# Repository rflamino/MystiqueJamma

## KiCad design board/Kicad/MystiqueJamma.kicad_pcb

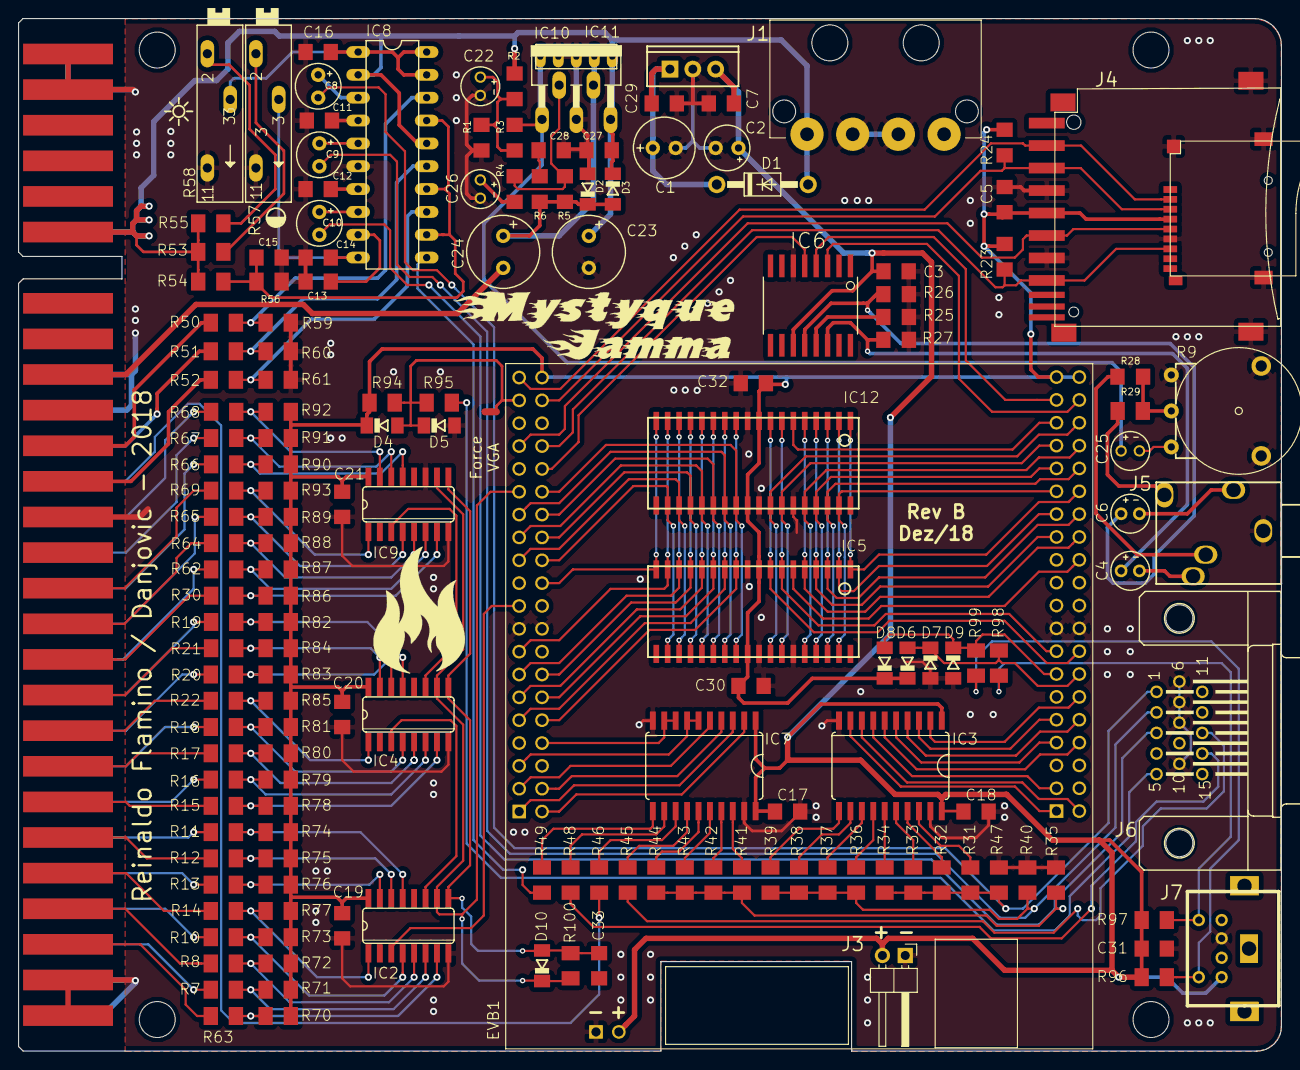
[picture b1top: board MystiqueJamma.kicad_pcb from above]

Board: 2 copper layers, 140.4 x 114.8 mm, 164 parts (0 on the bottom side), 171 nets.

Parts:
C1: 100uF; E2,5-7
C2, C8, C9, C10: 10uF; E2,5-5
C3, C5, C7, C11, C12, C13, C14, C15, C16, C17, C18, C19, C20, C21, C27, C29, C30, C31, C32: 100nF; C1206
C4, C6: 4.7uF; E2-4
C22: 22u; E2-4
C23: 100u/25V; E3,5-8
C24: 1000u/25V; E3,5-8
C25: 10uF; E2-4
C26: 2u2; E2-4
C28: 220nF; C1206
C33: 10n; C1206
D1: 1N4004; DO41-10
D2, D3: 1N4004; SOD80C
D4, D5, D6, D7, D8, D9, D10: 4148; SOD80C
EVB1: C4E6-K; E6V33_BELOW
IC1: 7805; TO220-IGO
IC2, IC4, IC9: 74HC4021D; SO16
IC3, IC7: 74LS245DW; SO20W
IC5, IC12: CY7C1049CV33; SOJV36-400
IC6: TDA1543T; SOIC-16NW
IC8: TLS1233; DIL20
IC10: TDA2030V; CB360
IC11: LA4425V; LA4425
J1: Conn_01x04; Molex_Mega-Fit_76829-0004_2x02_P5.70mm_Vertical
J2: Micro_SD_Card; 9P-SMD-W_-RING
J3: FPGA PWR; PinHeader_1x02_P2.54mm_Horizontal
J4: SDMMC06132; 06132
J5: 1503_09
J6: HF15H; HDF15H
J7: Mini-DIN-6; Mini_din6
K1: JAMMA-EDGE-MYSTIQUE; JAMMA-FULL
R1, R2, R3: 100k; R1206
R4, R28: 4k7; R1206
R5: 150k; R1206
R6: 1R; R1206
R7, R8, R10, R11, R12, R13, R14, R15, R16, R17, R18, R19, R20, R21, R22, R30, R35, R45, R46, R48, R49, R50, R51, R52, R62, R63, R64, R65, R66, R67, R68, R69, R95: 330; M1206
R9: 50k; M1001
R23, R24: 10k; R1206
R25: 1k; R1206
R26, R27: 2k; R1206
R29, R100: 4k7; M1206
R31, R36, R41: 420; M1206
R32, R37, R42: 785; M1206
R33, R38, R43: 1380; M1206
R34, R39, R44: 2230; M1206
R40, R47: 125; M1206
R53, R54, R55, R70, R71, R72, R73, R74, R75, R76, R77, R78, R79, R80, R81, R82, R83, R84, R85, R86, R87, R88, R89, R90, R91, R92, R93, R94: 10k; M1206
R56: 5k; M1206
R57, R58: 5k; SP19L
R59, R60, R61: 430; M1206
R96, R97: 2K2; M1206
R98, R99: 120; M1206

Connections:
+3V3: C5.1, C19.1, C20.1, C21.1, C30.1, C32.1, D4.C, D6.C, D8.C, EVB1.VCC1, EVB1.VCC2, EVB1.VCC3, IC2.16, IC4.16, IC5.9, IC5.27, IC9.16, IC12.9, IC12.27, J2.4, J4.4, R23.2, R24.2, R70.2, R71.2, R72.2, R73.2, R74.2, R75.2, R76.2, R77.2, R78.2, R79.2, R80.2, R81.2, R82.2, R83.2, R84.2, R85.2, R86.2, R87.2, R88.2, R89.2, R90.2, R91.2, R92.2, R93.2, R94.2
+5V: C2.+, C3.1, C7.1, C17.1, C18.1, C31.1, EVB1.5VCC, IC1.OUT, IC3.1, IC3.20, IC6.11, IC7.1, IC7.20, J3.2, J7.5, R96.2, R97.2
+12V: C23.+, C27.1, D1.A, D3.C, IC8.2, IC8.16, IC10.5, IC11.5, J1.1, K1.6, K1.F, R2.1, R53.2, R54.2, R55.2
/AUD-IN: C25.+, IC10.1, IC11.1, R3.2
/B0: EVB1.I0_30, IC7.2
/B1: EVB1.I0_28, IC7.3
/B2: EVB1.I0_32, IC7.4
/B3: EVB1.I0_31, IC7.5
/BURST_GATE: IC8.11, R49.2
/CNTR_CK_LAT: D10.C, EVB1.I0_68, IC2.10, IC4.10, IC9.10, R100.1
/CNTR_DAT: EVB1.I0_53, IC2.3
/COINSW1: K1.16, R69.2
/COINSW2: K1.T, R66.2
/DAC_VREF: IC6.13, R25.2
/G0: EVB1.I0_143, IC3.6
/G1: EVB1.I0_7, IC3.7
/G2: EVB1.I0_10, IC3.8
/G3: EVB1.I0_11, IC3.9
/HSY: EVB1.I0_33, IC7.6, IC7.7
/I2S_BCK: EVB1.I0_103, IC6.3
/I2S_DATA: EVB1.I0_71, IC6.5
/I2S_WS: EVB1.I0_101, IC6.4
/JAMMA-BLUE: K1.13, R52.2
/JAMMA-CSYNC: K1.P, R46.2
/JAMMA-GREEN: K1.N, R51.2
/JAMMA-RED: K1.12, R50.2
/JAMMA_AUDIO: R9.2, R28.2, R29.2
/JAMMA_SPK+: C24.-, K1.10
/LATCH: C33.1, D10.A, IC2.9, IC4.9, IC9.9, R100.2
/L_A: C6.+, IC6.12, R26.2
/L_AUDIO: C6.-, J5.2
/P1B1: K1.22, R15.2
/P1B2: K1.23, R12.2
/P1B3: K1.24, R14.2
/P1B4: K1.25, R8.2
/P1B5: K1.26, R63.2
/P1DW: K1.19, R21.2
/P1LH: K1.20, R22.2
/P1RH: K1.21, R17.2
/P1START: K1.17, R64.2
/P1UP: K1.18, R30.2
/P2B1: K1.Z, R16.2
/P2B2: K1.#A, R11.2
/P2B3: K1.#B, R13.2
/P2B4: K1.#C, R10.2
/P2B5: K1.#D, R7.2
/P2DW: K1.W, R19.2
/P2LH: K1.X, R20.2
/P2RH: K1.Y, R18.2
/P2START: K1.U, R65.2
/P2UP: K1.V, R62.2
/R0: EVB1.I0_137, IC3.2
/R1: EVB1.I0_142, IC3.3
/R2: EVB1.I0_141, IC3.4
/R3: EVB1.I0_144, IC3.5
/R_A: C4.+, IC6.14, R27.2
/R_AUDIO: C4.-, J5.3
/SD_CNT_SCLK: EVB1.I0_72, J2.5, J4.5
/SD_CS: EVB1.I0_100, J2.2, J4.1
/SD_DATAIN: EVB1.I0_99, J2.3, J4.2, R24.1
/SD_DATAOUT: EVB1.I0_88, J2.7, J4.7, R23.1
/SERVICE_SW: K1.R, R68.2
/SRAM_A0: EVB1.I0_114, IC5.1, IC12.1
/SRAM_A1: EVB1.I0_115, IC5.2, IC12.2
/SRAM_A2: EVB1.I0_119, IC5.3, IC12.3
/SRAM_A3: EVB1.I0_120, IC5.4, IC12.4
/SRAM_A4: EVB1.I0_121, IC5.5, IC12.5
/SRAM_A5: EVB1.I0_44, IC5.14, IC12.14
/SRAM_A6: EVB1.I0_50, IC5.15, IC12.15
/SRAM_A7: EVB1.I0_49, IC5.16, IC12.16
/SRAM_A8: EVB1.I0_51, IC5.17, IC12.17
/SRAM_A9: EVB1.I0_58, IC5.18, IC12.18
/SRAM_A10: EVB1.I0_60, IC5.20, IC12.20
/SRAM_A11: EVB1.I0_59, IC5.21, IC12.21
/SRAM_A12: EVB1.I0_65, IC5.22, IC12.22
/SRAM_A13: EVB1.I0_64, IC5.23, IC12.23
/SRAM_A14: EVB1.I0_67, IC5.24, IC12.24
/SRAM_A15: EVB1.I0_110, IC5.32, IC12.32
/SRAM_A16: EVB1.I0_111, IC5.33, IC12.33
/SRAM_A17: EVB1.I0_112, IC5.34, IC12.34
/SRAM_A18: EVB1.I0_113, IC5.35, IC12.35
/SRAM_CE1: EVB1.I0_125, IC5.6
/SRAM_CE2: EVB1.I0_104, IC12.6
/SRAM_IO0: EVB1.I0_133, IC5.7, IC12.7
/SRAM_IO1: EVB1.I0_132, IC5.8, IC12.8
/SRAM_IO2: EVB1.I0_43, IC5.11, IC12.11
/SRAM_IO3: EVB1.I0_42, IC5.12, IC12.12
/SRAM_IO4: EVB1.I0_66, IC5.25, IC12.25
/SRAM_IO5: EVB1.I0_69, IC5.26, IC12.26
/SRAM_IO6: EVB1.I0_105, IC5.29, IC12.29
/SRAM_IO7: EVB1.I0_106, IC5.30, IC12.30
/SRAM_WE: EVB1.I0_46, IC5.13, IC12.13
/TILT: K1.S, R67.2
/VGA-BLUE: C10.-, J6.3, R35.2, R41.2, R42.2, R43.2, R44.2
/VGA-GREEN: C9.-, J6.2, R36.2, R37.2, R38.2, R39.2, R40.2
/VGA-HSYNC: J6.13, R45.2
/VGA-RED: C8.-, J6.1, R31.2, R32.2, R33.2, R34.2, R47.2
/VGA-VSYNC: J6.14, R48.2
/VGA_DETECT: J6.5, R95.2
/VGA_DET_IN: D4.A, D5.C, EVB1.I0_91, R94.1, R95.1
/VSY: EVB1.I0_39, IC7.8, IC7.9
GND: C1.-, C2.-, C3.2, C5.2, C7.2, C11.2, C12.2, C13.2, C14.2, C15.2, C16.2, C17.2, C18.2, C19.2, C20.2, C21.2, C22.-, C23.-, C26.-, C27.2, C28.2, C29.2, C30.2, C31.2, C32.2, D2.A, D5.A, D7.A, D9.A, EVB1.GND1, EVB1.GND2, EVB1.GND3, EVB1.GND4, EVB1.GND5, IC1.GND, IC2.8, IC3.10, IC3.19, IC4.8, IC5.10, IC5.28, IC5.31, IC6.6, IC7.10, IC7.19, IC8.6, IC9.8, IC9.11, IC10.3, IC11.2, IC11.3, IC12.10, IC12.28, IC12.31, J1.2, J1.3, J2.6, J2.SHL@1, J2.SHL@2, J2.SHL@3, J3.1, J4.3, J4.6, J4.GP, J4.GP2, J5.1, J6.6, J6.7, J6.8, J6.10, J7.3, K1.1, K1.2, K1.14, K1.27, K1.28, K1.#E, K1.#F, K1.A, K1.B, K1.L, K1.M, R1.2, R9.1, R9.G1, R9.G2, R25.1, R26.1, R27.1, R35.1, R40.1, R47.1, R56.1, R57.A, R58.A, R59.1, R60.1, R61.1
unnamed: C1.+, C29.1, D1.C, IC1.IN
unnamed: C8.+, IC8.3
unnamed: C9.+, IC8.5
unnamed: C10.+, IC8.8
unnamed: C11.1, IC8.4
unnamed: C12.1, IC8.7
unnamed: C13.1, IC8.9
unnamed: C14.1, IC8.10, R57.S
unnamed: C15.1, IC8.12, IC8.14, IC8.17, R54.1, R56.2
unnamed: C16.1, IC8.1, IC8.19, IC8.20, R58.S
unnamed: C22.+, R1.1, R2.2, R3.1
unnamed: C24.+, D2.C, D3.A, IC10.4, IC11.4, R5.1, R6.1
unnamed: C25.-, R9.3
unnamed: C26.+, R4.2
unnamed: C28.1, R6.2
unnamed: IC2.1, R14.1, R77.1
unnamed: IC2.4, R10.1, R73.1
unnamed: IC2.5, R8.1, R72.1
unnamed: IC2.6, R7.1, R71.1
unnamed: IC2.7, R63.1, R70.1
unnamed: IC2.11, IC4.3
unnamed: IC2.13, R11.1, R74.1
unnamed: IC2.14, R12.1, R75.1
unnamed: IC2.15, R13.1, R76.1
unnamed: IC3.11, R39.1
unnamed: IC3.12, R38.1
unnamed: IC3.13, R37.1
unnamed: IC3.14, R36.1
unnamed: IC3.15, R34.1
unnamed: IC3.16, R33.1
unnamed: IC3.17, R32.1
unnamed: IC3.18, R31.1
unnamed: IC4.1, R22.1, R85.1
unnamed: IC4.4, R18.1, R81.1
unnamed: IC4.5, R17.1, R80.1
unnamed: IC4.6, R16.1, R79.1
unnamed: IC4.7, R15.1, R78.1
unnamed: IC4.11, IC9.3
unnamed: IC4.13, R19.1, R82.1
unnamed: IC4.14, R20.1, R83.1
unnamed: IC4.15, R21.1, R84.1
unnamed: IC7.11, R49.1
unnamed: IC7.12, R48.1
unnamed: IC7.13, R46.1
unnamed: IC7.14, R45.1
unnamed: IC7.15, R44.1
unnamed: IC7.16, R43.1
unnamed: IC7.17, R42.1
unnamed: IC7.18, R41.1
unnamed: IC8.13, R52.1, R61.2
unnamed: IC8.15, R51.1, R60.2
unnamed: IC8.18, R50.1, R59.2
unnamed: IC9.1, R69.1, R93.1
unnamed: IC9.4, R65.1, R89.1
unnamed: IC9.5, R64.1, R88.1
unnamed: IC9.6, R62.1, R87.1
unnamed: IC9.7, R30.1, R86.1
unnamed: IC9.13, R66.1, R90.1
unnamed: IC9.14, R67.1, R91.1
unnamed: IC9.15, R68.1, R92.1
unnamed: IC10.2, R4.1, R5.2
unnamed: J5.4, R29.1
unnamed: J5.5, R28.1
unnamed: J7.1, R97.1, R98.1
unnamed: J7.6, R96.1, R99.1
unnamed: R53.1, R57.E
unnamed: R55.1, R58.E
PS2CK: D6.A, D7.C, EVB1.I0_135, R98.2
PS2DAT: D8.A, D9.C, EVB1.I0_136, R99.2

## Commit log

2018-08-28 MystiqueJamma files
    initial commit
2018-08-28 created folder board
2018-08-28 included jamma eagle lib
2018-08-28 included pdf file
2018-09-03 jamma spacing change
2018-09-10 included sdcard
2018-09-10 docs
2018-09-12 changed sram ic
2018-09-16 wiring up!
2018-09-16 pictures
2018-09-17 pdf file
2018-09-17 added gitignore for eagle files
2018-09-18 deleted temp files
2018-09-22 documents
2018-09-22 photos
2018-09-23 changed the jamma connector and included audio TDA1543
2018-09-23 fpga board pictures
2018-09-24 protel 99 file from fpga board
2018-09-25 audio circuit update
2018-09-25 audio circuit
2018-09-25 Eagle library for FPGA board
    Eagle library for FPGA board. Dimensions and components placement as received from manufacturer and have small misalignments (< 5 mils)
2018-09-25 video circuit
2018-09-25 included the FPGA board library
2018-09-25 Added reference Pinouts
    Added reference pinouts, changed board outline to TPlace like a component
2018-09-26 Added TLS1233 video amplifier IC library
2018-09-26 more video docs
2018-09-26 Added spreadsheet with pin usage
2018-09-26 xls list
2018-09-27 kicad project
2018-09-27 kicad board layout
2018-09-27 kicad
2018-09-28 Shift registers to read controllers, new libs
2018-09-28 Updated pinouts, added docs
2018-09-28 Added DAC calculation tab on spreadsheet
2018-10-07 FPGA board pins now defined
2018-10-10 Added volume potentiometer footprint
2018-10-23 Added MOLEX power connector
2018-10-23 Added edge cut for JTAG header
2018-10-25 Edge connector pins associated with shift registers
2018-10-26 First completed layout
2018-10-31 routing and footprints enhancement
2018-10-31 discarded old file
2018-11-07 Added Mini DIN6 Connector
2018-11-09 Added Logo, arranged component labels
2018-11-12 Removed old directory updated schematics
2018-11-12 board pictures tryout
2018-11-23 Updated component values
2018-11-25 vga test
2018-11-25 VGA test core files
2018-11-30 Added second SRAM, Match FPGA IO usage with board available pins
2018-12-05 Circuit update and cleanup
    Added second SRAM, changed VGA detect to FPGA instead of shift registers, added solder joint to force VGA mode, added RC-Network to Shift Register clock signal to allow same line to control LATCH sig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
2018-12-19 Added Micro SD card connector
